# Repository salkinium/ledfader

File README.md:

Standalone driver for 32 LEDs
=============================

This board should drive 32 LEDs using 12bit resolution at a ~2kHz frequency
using two TLC5940s controlled by a ATmega328.
There is one button and a vibration sensor, to changes modes and save power (both optional).
The serial can be accessed (so Arduino support should be possible).

The software is written using the [XPCC library][xpcc], for its TLC5940 driver,
gamma correction and workflow classes.

Organisation
------------

This repository is organized as follows:

-	The *hardware* folder contains the EAGLE schematics and layouts of the
	electronic assembly, with parts list and datasheets.
- 	The *software* folder contains the software for the microcontroller.

[xpcc]: http://xpcc.kreatives-chaos.com

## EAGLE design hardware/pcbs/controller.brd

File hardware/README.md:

LED driver hardware
===================

The ATmega328P can fade 32 LEDs using two TLC5940 12bit LED drivers.

Programmer
----------

The ATmega is programmed using the standard ISP interface, however to save space,
a smaller footprint is used.
On standard PCBs with 1.6mm thickness, the board fits exacly between to RM 2.00 pins,
so I just use a 2x3 RM 2.00 pin header to attach my programmer to it from the side.
This takes up a *lot* less space and the connection is secure enough.

Parts List and Description
--------------------------

### Battery charger

Using [Sparkfuns USB Lipo charger](
https://www.sparkfun.com/products/10401).

### Battery

This circuit can be powered by a standard 3.7V LiPo/LiIon rechargeable battery **without** voltage regulator.

### Microcontroller

A ATmega328P in a 32-pin TQFP package is used.

### Resonator

Small footprint, reasonable frequency stability of ±0.5% at 8MHz: CSTCE 8,00.

Some background on the maximum possible frequency:
The 3.7V LiPo battery voltage can be anywhere between 3V to 4.2V.

The ATmega328P is rated at 10Mhz @ 2.7V and 20Mhz @ 4.5V.
For 3V the maximum frequency is already above 10MHz, so we're fine.  

The lowest voltage for 8MHz is:  
(8MHz - 4MHz) * (2.7 - 1.8)V / (10 - 4)MHz + 1.8V = 2.4V

But the TLC5940 requires 3V minimum voltage, so never mind.

### Tactile Switch

A light touch switch from Panasonic is used:  
EVQPS with J-bend terminals: EVQPSG02K without Boss

### Vibration sensor

MVS 0608.02 is used.  
It's not widely available so you can leave it out.

### Other parts

Some 0603 and 0805 resistors and capacitors are used.

A RM 2.00 mm In-System Programming socket is used.

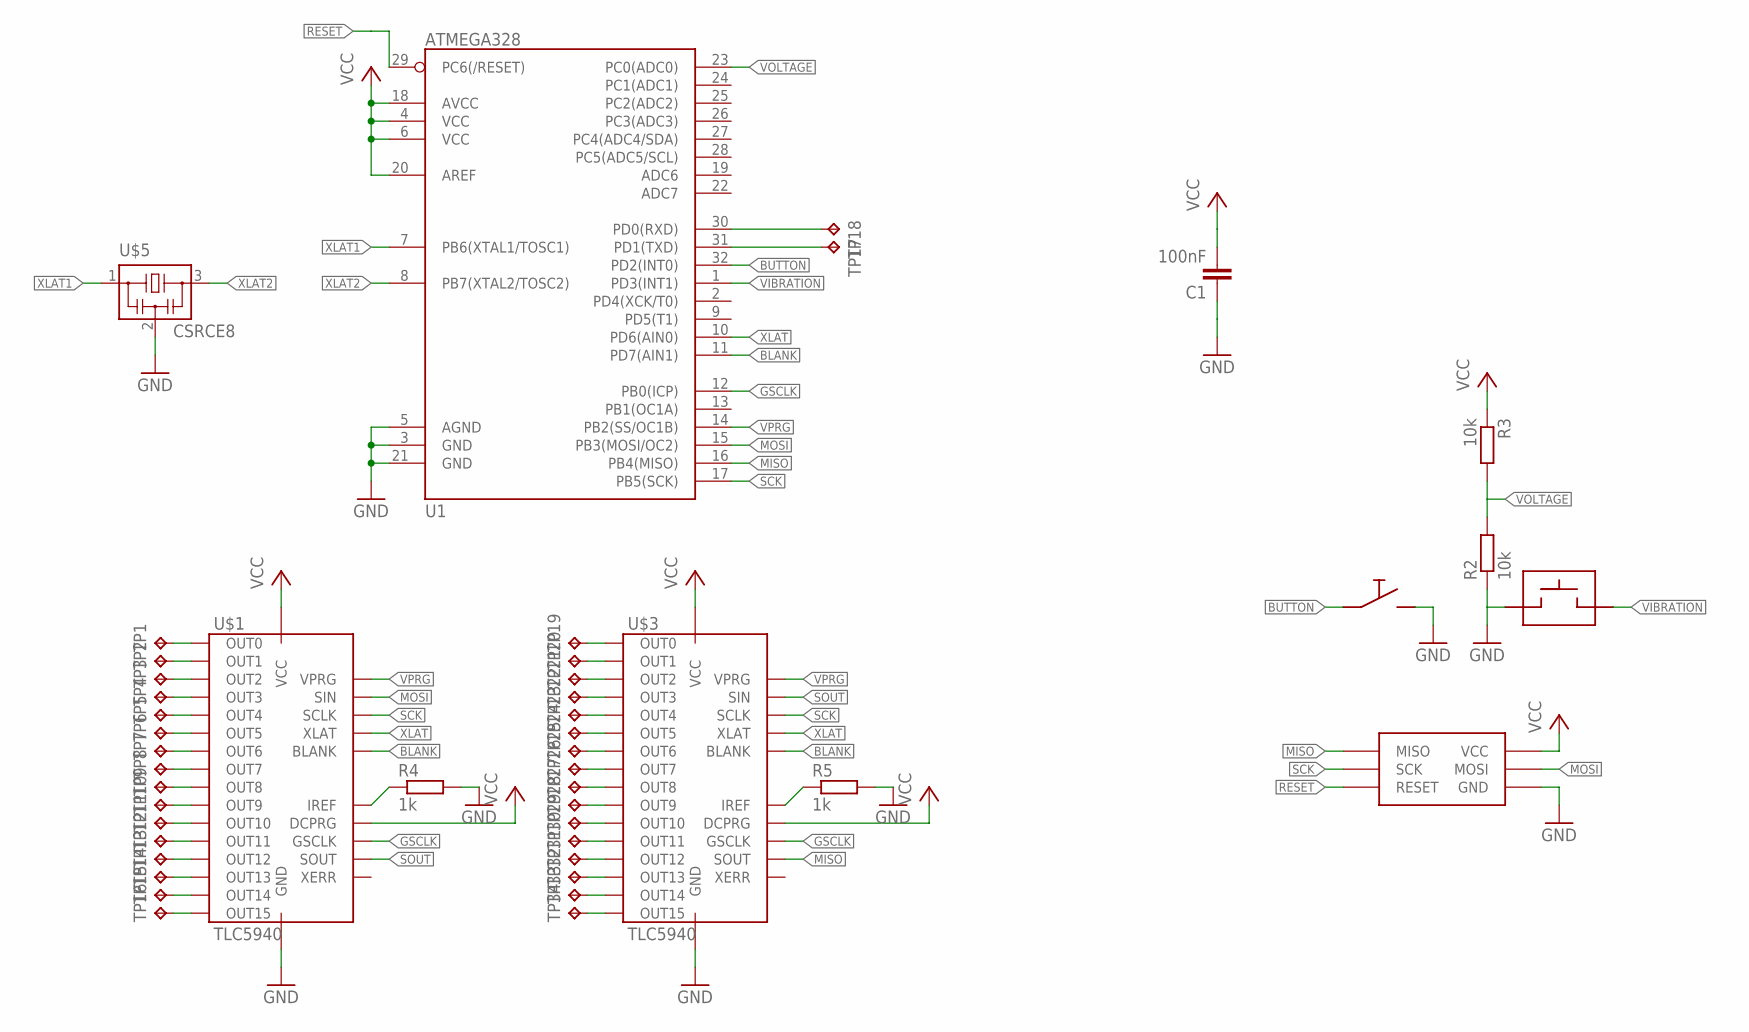
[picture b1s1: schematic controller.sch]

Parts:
C1: 100nF; C0603
R2, R3: 10k; R0603
R4, R5: 1k; R0603
TP1, TP2, TP3, TP4, TP5, TP6, TP7, TP8, TP9, TP10, TP11, TP12, TP13, TP14, TP15, TP16, TP17, TP18, TP19, TP20, TP21, TP22, TP23, TP24, TP25, TP26, TP27, TP28, TP29, TP30, TP31, TP32, TP33, TP34: TPTP15SQ; TP15SQ
U1: ATMEGA328; TQFP32-08
U$1, U$3: TLC5940; PWP_28PIN
U$2: ISP_SPECIALS; ISP_RM2_00_STRAIGHT
U$4: MOTION_SENSOR; MOTION
U$5: CSRCE8; CSTCE_G
U$6: SWITCH; EVQPSG02K

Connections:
BLANK: U1.11 (PD7(AIN1)), U$1.P2 (BLANK), U$3.P2 (BLANK)
BUTTON: U1.32 (PD2(INT0)), U$6.A, U$6.A@2
GND: C1.1, R2.1, R4.2, R5.2, U1.3 (GND), U1.5 (AGND), U1.21 (GND), U$1.P1 (GND), U$1.P29 (GND), U$2.VCC (GND), U$3.P1 (GND), U$3.P29 (GND), U$4.P$1 (IN), U$5.2, U$6.B, U$6.B@2
GSCLK: U1.12 (PB0(ICP)), U$1.P25 (GSCLK), U$3.P25 (GSCLK)
MISO: U1.16 (PB4(MISO)), U$2.RESET (MISO), U$3.P24 (SOUT)
MOSI: U1.15 (PB3(MOSI/OC2)), U$1.P5 (SIN), U$2.MOSI
unnamed: TP1.TP, U$1.P7 (OUT0)
unnamed: TP2.TP, U$1.P8 (OUT1)
unnamed: TP3.TP, U$1.P9 (OUT2)
unnamed: TP4.TP, U$1.P10 (OUT3)
unnamed: TP5.TP, U$1.P11 (OUT4)
unnamed: TP6.TP, U$1.P12 (OUT5)
unnamed: R4.1, U$1.P27 (IREF)
unnamed: TP7.TP, U$1.P13 (OUT6)
unnamed: TP8.TP, U$1.P14 (OUT7)
unnamed: TP9.TP, U$1.P15 (OUT8)
unnamed: TP10.TP, U$1.P16 (OUT9)
unnamed: TP11.TP, U$1.P17 (OUT10)
unnamed: TP12.TP, U$1.P18 (OUT11)
unnamed: TP13.TP, U$1.P19 (OUT12)
unnamed: TP14.TP, U$1.P20 (OUT13)
unnamed: TP15.TP, U$1.P21 (OUT14)
unnamed: TP16.TP, U$1.P22 (OUT15)
unnamed: R5.1, U$3.P27 (IREF)
unnamed: TP19.TP, U$3.P7 (OUT0)
unnamed: TP20.TP, U$3.P8 (OUT1)
unnamed: TP21.TP, U$3.P9 (OUT2)
unnamed: TP22.TP, U$3.P10 (OUT3)
unnamed: TP23.TP, U$3.P11 (OUT4)
unnamed: TP24.TP, U$3.P12 (OUT5)
unnamed: TP25.TP, U$3.P13 (OUT6)
unnamed: TP26.TP, U$3.P14 (OUT7)
unnamed: TP27.TP, U$3.P15 (OUT8)
unnamed: TP28.TP, U$3.P16 (OUT9)
unnamed: TP29.TP, U$3.P17 (OUT10)
unnamed: TP30.TP, U$3.P18 (OUT11)
unnamed: TP31.TP, U$3.P19 (OUT12)
unnamed: TP32.TP, U$3.P20 (OUT13)
unnamed: TP33.TP, U$3.P21 (OUT14)
unnamed: TP34.TP, U$3.P22 (OUT15)
RESET: U1.29 (PC6(/RESET)), U$2.MISO (RESET)
RX: TP18.TP, U1.30 (PD0(RXD))
SCK: U1.17 (PB5(SCK)), U$1.P4 (SCLK), U$2.SCK, U$3.P4 (SCLK)
SOUT: U$1.P24 (SOUT), U$3.P5 (SIN)
TX: TP17.TP, U1.31 (PD1(TXD))
VCC: C1.2, R3.1, U1.4 (VCC), U1.6 (VCC), U1.18 (AVCC), U1.20 (AREF), U$1.P26 (DCPRG), U$1.P28 (VCC), U$2.GND (VCC), U$3.P26 (DCPRG), U$3.P28 (VCC)
VIBRATION: U1.1 (PD3(INT1)), U$4.P$2 (OUT)
VOLTAGE: R2.2, R3.2, U1.23 (PC0(ADC0))
VPRG: U1.14 (PB2(SS/OC1B)), U$1.P6 (VPRG), U$3.P6 (VPRG)
XLAT: U1.10 (PD6(AIN0)), U$1.P3 (XLAT), U$3.P3 (XLAT)
XLAT1: U1.7 (PB6(XTAL1/TOSC1)), U$5.1
XLAT2: U1.8 (PB7(XTAL2/TOSC2)), U$5.3

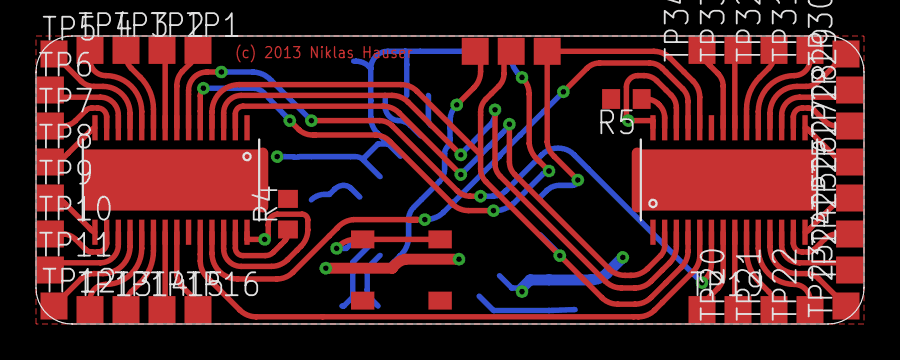
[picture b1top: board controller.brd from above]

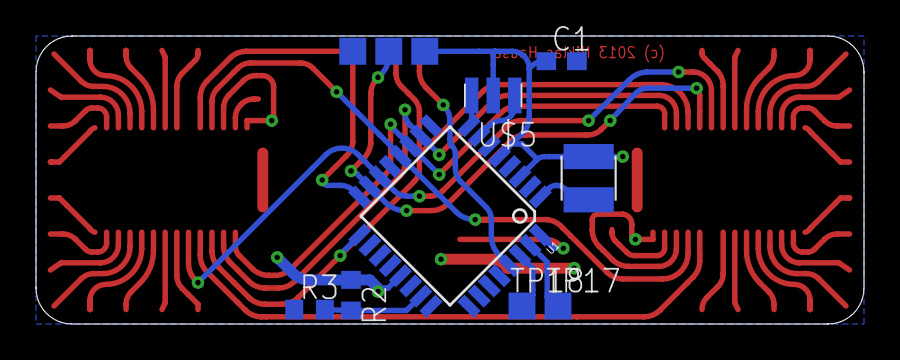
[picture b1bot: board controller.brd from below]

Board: 2 copper layers, 46.0 x 16.0 mm, 46 parts (8 on the bottom side), 52 nets.

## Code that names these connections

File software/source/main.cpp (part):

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// IO #########################################################################
//
//                     +------------+
// (MOTION/INT1) PD3  1|o           |24  PC1
//               PD4  2|            |23  PC0 (ADC0/VOLTAGE)
//               GND  3|            |22  ADC7
//               VCC  4|            |21  GND
//               GND  5|            |20  AREF
//               VCC  6|            |19  ADC6
//       (XLAT1) PB6  7|            |18  AVCC
//       (XLAT2) PB7  8|            |17  PB5 (SCK)
//                     +------------+
//
//                     +------------+
//              PD5   9|           o|32  PD2 (BUTTON/INT0)
//       (XLAT) PD6  10|            |31  PD1 (TXD)
//      (BLANK) PD7  11|            |30  PD0 (RXD)
//      (GSCLK) PB0  12|            |29  PC6 (RESET)
//              PB1  13|            |28  PC5
//      (VPROG) PB2  14|            |27  PC4
//       (MOSI) PB3  15|            |26  PC3
//       (MISO) PB4  16|            |25  PC2
//                     +------------+


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GPIO__INPUT(MOTION, D, 3);

GPIO__OUTPUT(VPROG, B, 2);
GPIO__OUTPUT(XLAT, D, 6);
GPIO__OUTPUT(BLANK, D, 7);
GPIO__OUTPUT(GSCLK, B, 0);

GPIO__INPUT(VOLTAGE, C, 0);

GPIO__INPUT(RESET, C, 6);
GPIO__OUTPUT(SCK, B, 5);
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	TXD::setOutput();
	RXD::setInput();
	VOLTAGE::setInput();
	BLANK::setOutput(xpcc::gpio::LOW);
	SCK::setOutput();
	MOSI::setOutput();
	MISO::setInput();
	VPROG::setOutput(xpcc::gpio::LOW);
	XLAT::setOutput(xpcc::gpio::LOW);
	
	LedSpi::initialize(LedSpi::MODE_0, LedSpi::PRESCALER_2);
	set_sleep_mode(SLEEP_MODE_IDLE);
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		if (!inMotion && fadeOutTimer.isExpired())
		{
			// turn off all LED driver outputs
			BLANK::set(xpcc::gpio::HIGH);
			// go to deep sleep
			set_sleep_mode(SLEEP_MODE_PWR_DOWN);
			justWokeUp = true;
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
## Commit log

2013-01-26 Initial commit.
2013-01-26 Add EAGLE libraries and layouts.
2013-01-26 Add firmware source.
2013-01-26 Add all LED controllers.
2013-01-30 Add alternative, smaller layout of PCB. The PCB has less good thermal capabilities though.
2013-02-25 Add xpcc as a submodule.
2013-02-25 Add resistor and capacitor values to schematic.
2013-02-25 Fix compilation error.
2013-02-26 Add blank pin driver. New initialization sequence. Add new led driver classes.
2013-03-05 Add VPROG pin to controller2.
2013-03-05 Add a new controller design v3.
2013-03-05 Disconnect thermal pad from GND. Add restrictions for easier soldering.
2013-03-25 Remove first two pcb iterations and replace with the third working one.
2013-03-25 Add use of Button to code. Add sleep mode incl. power down for deep sleep.
2013-03-25 Add Led for Button interaction.
2013-03-25 Update all READMEs.
2013-03-26 Add ISP programmer footprint information.
2013-03-26 Add button debounce code. Dot Correction now set atomically. Added dot correction for all required leds.
2013-03-26 Add delayed strobe, beacon and pulse start. Fix issue when coming out of deep sleep.
2013-03-26 Update to newest XPCC version.
2013-03-27 Add wake up filter to light up only after a certain time of continuos motion. Fix button state after wakeup.

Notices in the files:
hardware/pcbs/controller.brd:
(c) 2013 Niklas Hauser
